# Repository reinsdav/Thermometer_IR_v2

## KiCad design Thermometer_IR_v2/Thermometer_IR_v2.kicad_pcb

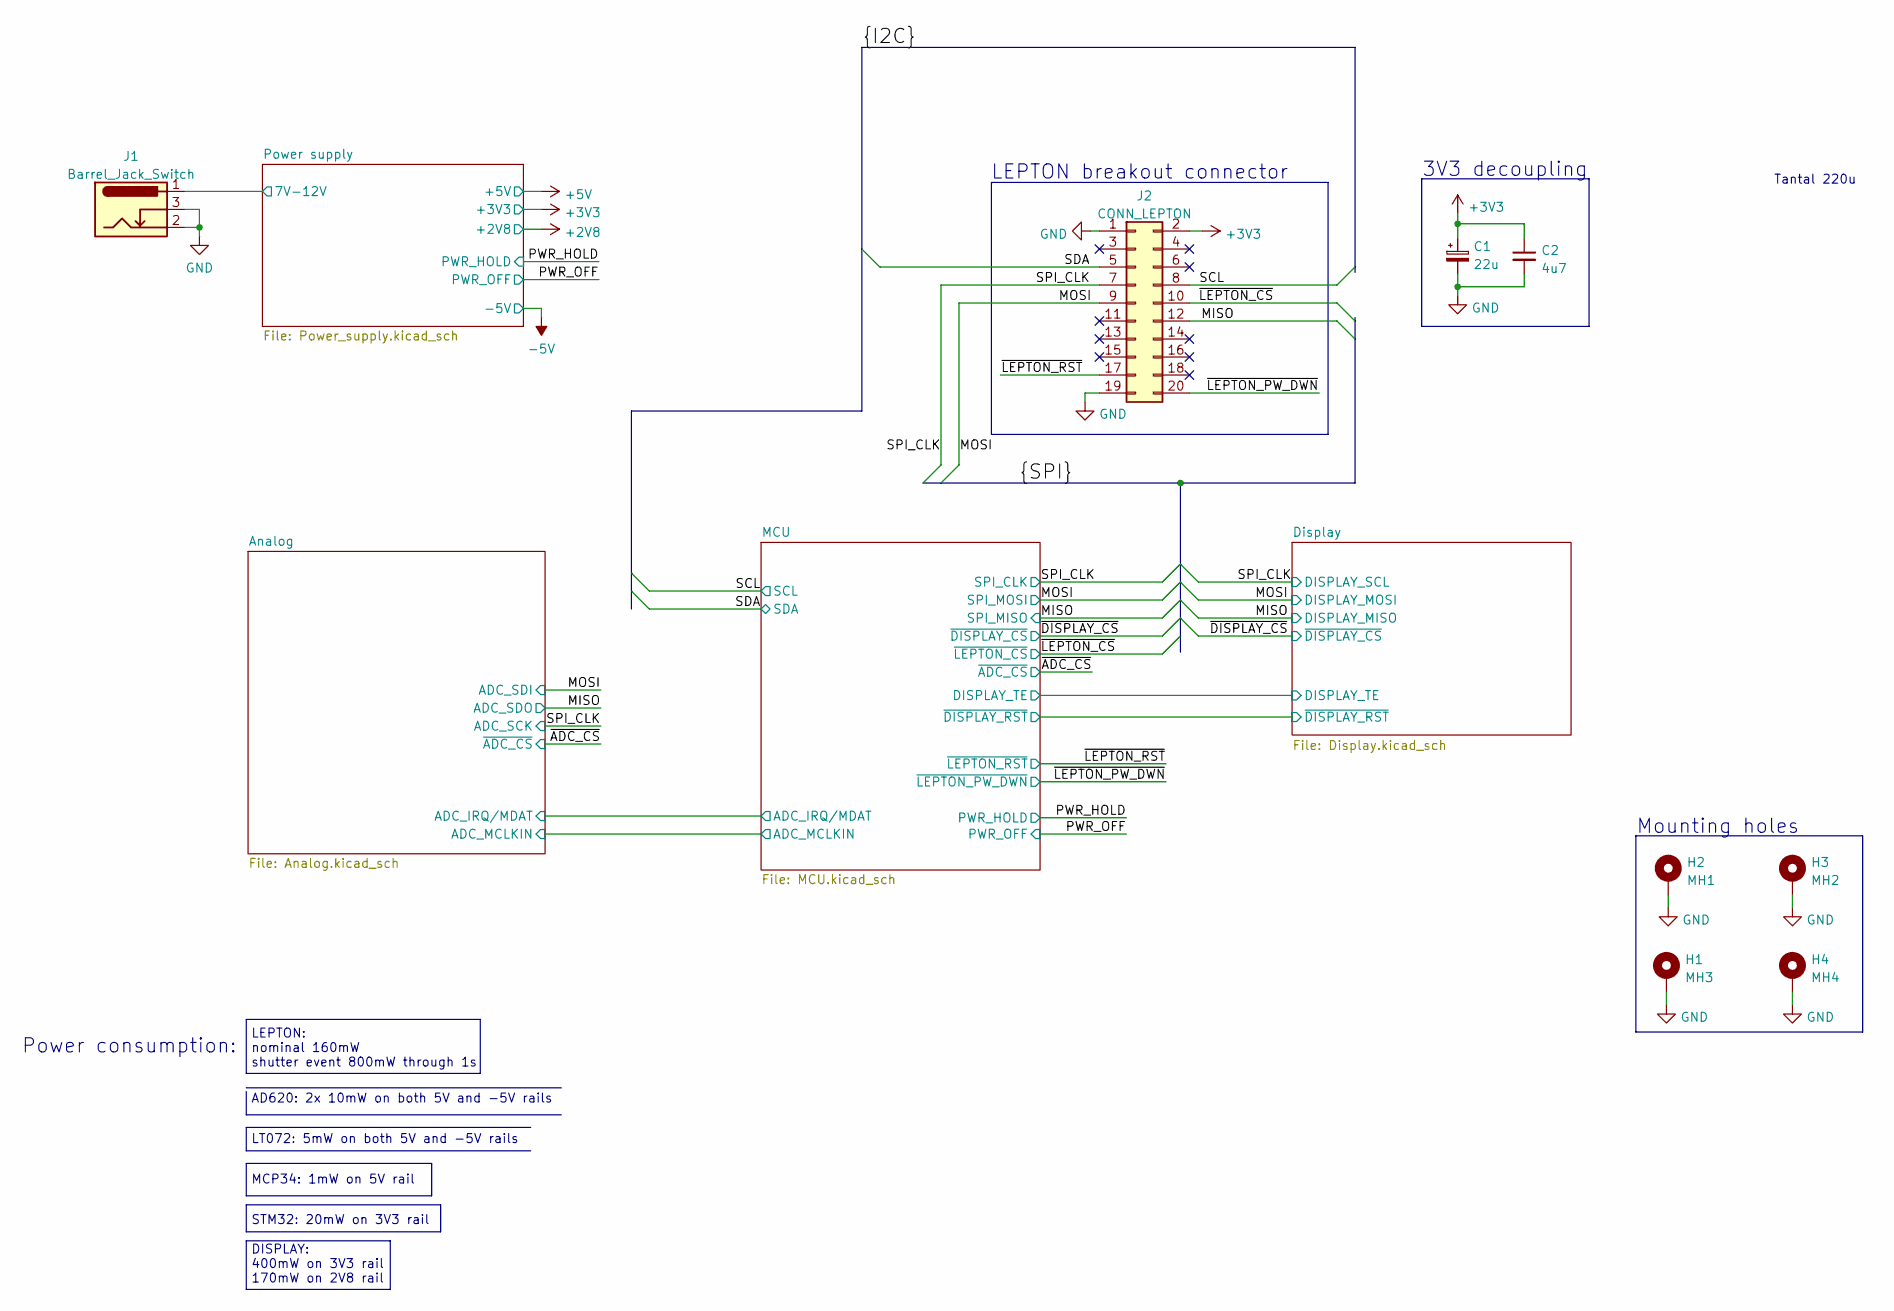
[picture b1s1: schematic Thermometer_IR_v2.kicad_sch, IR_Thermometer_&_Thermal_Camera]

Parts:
C1: 22u; CP_Elec_4x5.4
C2: 4u7; C_0805_2012Metric
H1: MH3; MountingHole_3mm_Pad_Via
H2: MH1; MountingHole_3mm_Pad_Via
H3: MH2; MountingHole_3mm_Pad_Via
H4: MH4; MountingHole_3mm_Pad_Via
J1: Barrel_Jack_Switch; BarrelJack_CLIFF_FC681465S_SMT_Horizontal
J2: CONN_LEPTON; PinSocket_2x10_P2.54mm_Horizontal

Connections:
+3V3: C1.1, C2.1, J2.2; also elsewhere on the board
/MISO: J2.12; also elsewhere on the board
/MOSI: J2.9; also elsewhere on the board
/Power supply/7V-12V: J1.1; also elsewhere on the board
/SCL: J2.8; also elsewhere on the board
/SDA: J2.5; also elsewhere on the board
/SPI_CLK: J2.7; also elsewhere on the board
/~LEPTON_CS: J2.10; also elsewhere on the board
/~LEPTON_PW_DWN: J2.20; also elsewhere on the board
/~LEPTON_RST: J2.17; also elsewhere on the board
GND: C1.2, C2.2, H1.1, H2.1, H3.1, H4.1, J1.2, J1.3, J2.1, J2.19; also elsewhere on the board

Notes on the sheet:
LT072: 5mW on both 5V and -5V rails
Power consumption:
STM32: 20mW on 3V3 rail
DISPLAY: 400mW on 3V3 rail 170mW on 2V8 rail
MCP34: 1mW on 5V rail
AD620: 2x 10mW on both 5V and -5V rails
3V3 decoupling
LEPTON breakout connector
Tantal 220u
LEPTON: nominal 160mW shutter event 800mW through 1s
Mounting holes

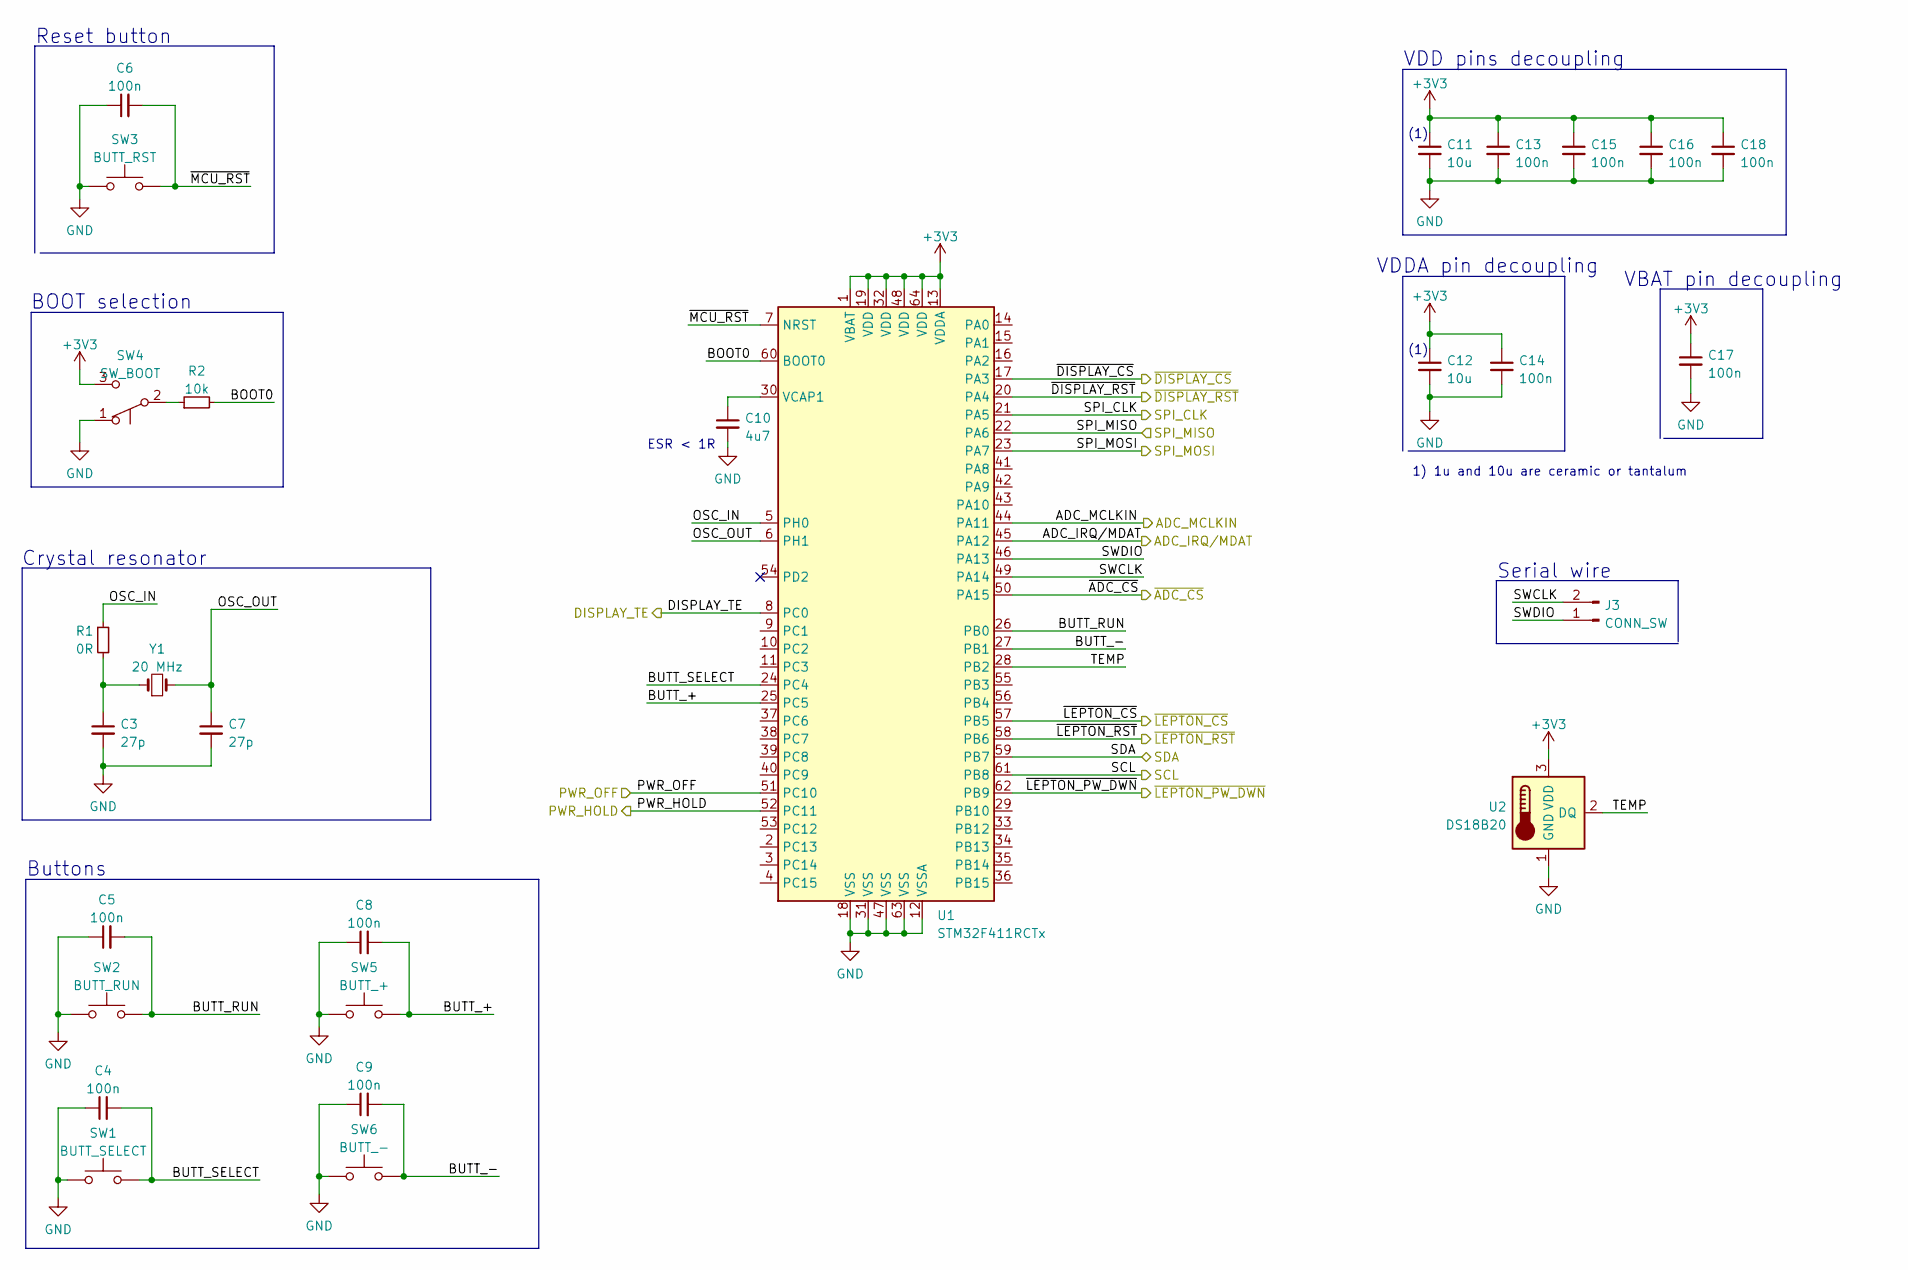
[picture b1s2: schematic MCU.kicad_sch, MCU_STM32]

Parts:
C3, C7: 27p; C_0805_2012Metric
C4, C5, C6, C8, C9, C13, C14, C15, C16, C17, C18: 100n; C_0805_2012Metric
C10: 4u7; C_0805_2012Metric
C11, C12: 10u; C_1206_3216Metric
J3: CONN_SW; PinHeader_1x02_P2.54mm_Vertical
R1: 0R; R_0805_2012Metric
R2: 10k; R_0805_2012Metric
SW1: BUTT_SELECT; SW_SPST_TL3305C
SW2: BUTT_RUN; SW_SPST_TL3305C
SW3: BUTT_RST; SW_SPST_TL3305C
SW4: SW_BOOT; SolderJumper-3_P1.3mm_Open_RoundedPad1.0x1.5mm_NumberLabels
SW5: BUTT_+; SW_SPST_TL3305C
SW6: BUTT_-; SW_SPST_TL3305C
U1: STM32F411RCTx; LQFP-64_10x10mm_P0.5mm
U2: DS18B20; TO-92_Inline
Y1: 20 MHz; Crystal_SMD_HC49-SD

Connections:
+3V3: C11.1, C12.1, C13.1, C14.1, C15.1, C16.1, C17.1, C18.1, SW4.3 (C), U1.1 (VBAT), U1.13 (VDDA), U1.19 (VDD), U1.32 (VDD), U1.48 (VDD), U1.64 (VDD), U2.3 (VDD); also elsewhere on the board
/Analog/ADC_IRQ/MDAT: U1.45 (PA12); also elsewhere on the board
/Analog/ADC_MCLKIN: U1.44 (PA11); also elsewhere on the board
/MCU/BOOT0: R2.2, U1.60 (BOOT0)
/MCU/BUTT_+: C8.2, SW5.2, U1.25 (PC5)
/MCU/BUTT_-: C9.2, SW6.2, U1.27 (PB1)
/MCU/BUTT_RUN: C5.2, SW2.2, U1.26 (PB0)
/MCU/BUTT_SELECT: C4.2, SW1.2, U1.24 (PC4)
/MCU/DISPLAY_TE: U1.8 (PC0); also elsewhere on the board
/MCU/OSC_IN: R1.1, U1.5 (PH0)
/MCU/OSC_OUT: C7.1, U1.6 (PH1), Y1.2
/MCU/SWCLK: J3.2, U1.49 (PA14)
/MCU/SWDIO: J3.1, U1.46 (PA13)
/MCU/TEMP: U1.28 (PB2), U2.2 (DQ)
/MCU/~DISPLAY_RST: U1.20 (PA4); also elsewhere on the board
/MCU/~MCU_RST: C6.2, SW3.2, U1.7 (NRST)
/MISO: U1.22 (PA6); also elsewhere on the board
/MOSI: U1.23 (PA7); also elsewhere on the board
/PWR_HOLD: U1.52 (PC11); also elsewhere on the board
/PWR_OFF: U1.51 (PC10); also elsewhere on the board
/SCL: U1.61 (PB8); also elsewhere on the board
/SDA: U1.59 (PB7); also elsewhere on the board
/SPI_CLK: U1.21 (PA5); also elsewhere on the board
/~ADC_CS: U1.50 (PA15); also elsewhere on the board
/~DISPLAY_CS: U1.17 (PA3); also elsewhere on the board
/~LEPTON_CS: U1.57 (PB5); also elsewhere on the board
/~LEPTON_PW_DWN: U1.62 (PB9); also elsewhere on the board
/~LEPTON_RST: U1.58 (PB6); also elsewhere on the board
GND: C3.2, C4.1, C5.1, C6.1, C7.2, C8.1, C9.1, C10.2, C11.2, C12.2, C13.2, C14.2, C15.2, C16.2, C17.2, C18.2, SW1.1, SW2.1, SW3.1, SW4.1 (A), SW5.1, SW6.1, U1.12 (VSSA), U1.18 (VSS), U1.31 (VSS), U1.47 (VSS), U1.63 (VSS), U2.1 (GND); also elsewhere on the board
unnamed: C3.1, R1.2, Y1.1
unnamed: C10.1, U1.30 (VCAP1)
unnamed: R2.1, SW4.2 (B)

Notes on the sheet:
Serial wire
VBAT pin decoupling
(1)
VDDA pin decoupling
1) 1u and 10u are ceramic or tantalum
BOOT selection
VDD pins decoupling
Buttons
Crystal resonator
Reset button
ESR < 1R

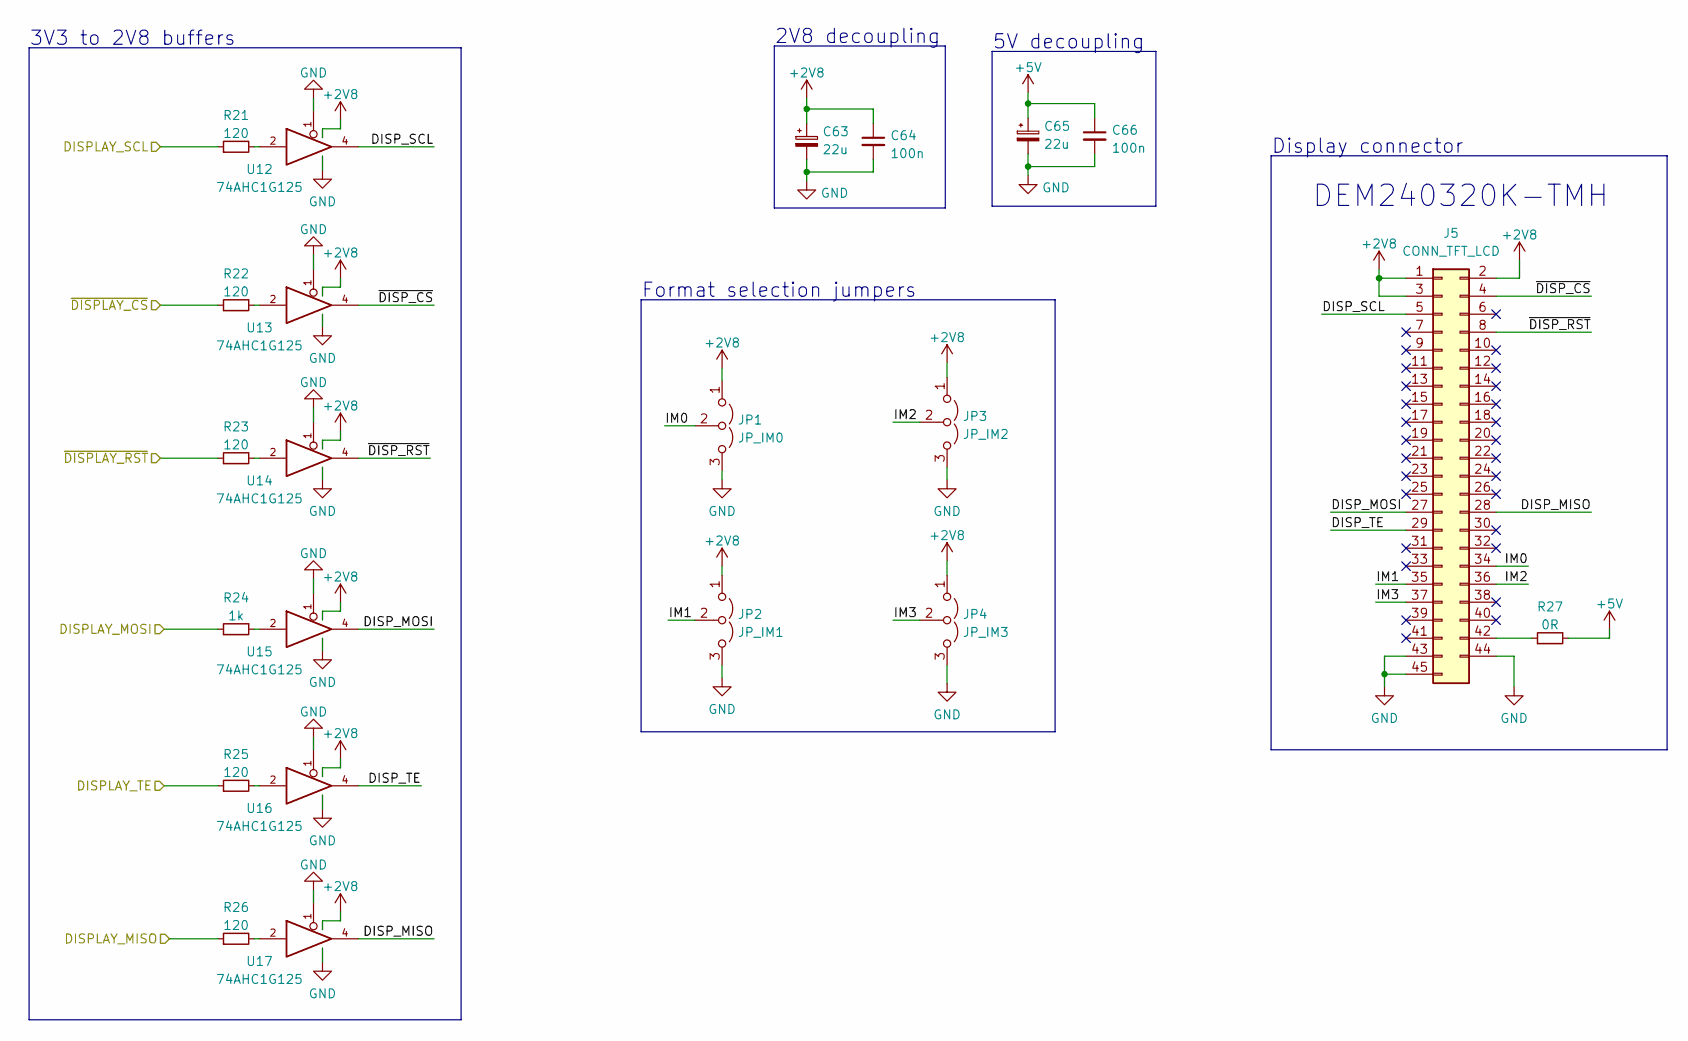
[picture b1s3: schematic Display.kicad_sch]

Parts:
C63, C65: 22u; CP_Elec_4x5.4
C64, C66: 100n; C_0805_2012Metric
J5: CONN_TFT_LCD; Hirose_FH12-45S-0.5SH_1x45-1MP_P0.50mm_Horizontal
JP1: JP_IM0; SolderJumper-3_P1.3mm_Open_RoundedPad1.0x1.5mm_NumberLabels
JP2: JP_IM1; SolderJumper-3_P1.3mm_Open_RoundedPad1.0x1.5mm_NumberLabels
JP3: JP_IM2; SolderJumper-3_P1.3mm_Open_RoundedPad1.0x1.5mm_NumberLabels
JP4: JP_IM3; SolderJumper-3_P1.3mm_Open_RoundedPad1.0x1.5mm_NumberLabels
R21, R22, R23, R25, R26: 120; R_0805_2012Metric
R24: 1k; R_0805_2012Metric
R27: 0R; R_0805_2012Metric
U12, U13, U14, U15, U16, U17: 74AHC1G125; SOT-353_SC-70-5

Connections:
+2V8: C63.1, C64.1, J5.1, J5.2, J5.3, JP1.1 (A), JP2.1 (A), JP3.1 (A), JP4.1 (A), U12.5 (VCC), U13.5 (VCC), U14.5 (VCC), U15.5 (VCC), U16.5 (VCC), U17.5 (VCC); also elsewhere on the board
+5V: C65.1, C66.1, R27.2; also elsewhere on the board
/Display/DISP_MISO: J5.28, U17.4
/Display/DISP_MOSI: J5.27, U15.4
/Display/DISP_SCL: J5.5, U12.4
/Display/DISP_TE: J5.29, U16.4
/Display/IM0: J5.34, JP1.2 (C)
/Display/IM1: J5.35, JP2.2 (C)
/Display/IM2: J5.36, JP3.2 (C)
/Display/IM3: J5.37, JP4.2 (C)
/Display/~DISP_CS: J5.4, U13.4
/Display/~DISP_RST: J5.8, U14.4
/MCU/DISPLAY_TE: R25.1; also elsewhere on the board
/MCU/~DISPLAY_RST: R23.1; also elsewhere on the board
/MISO: R26.1; also elsewhere on the board
/MOSI: R24.1; also elsewhere on the board
/SPI_CLK: R21.1; also elsewhere on the board
/~DISPLAY_CS: R22.1; also elsewhere on the board
GND: C63.2, C64.2, C65.2, C66.2, J5.43, J5.44, J5.45, JP1.3 (B), JP2.3 (B), JP3.3 (B), JP4.3 (B), U12.1, U12.3 (GND), U13.1, U13.3 (GND), U14.1, U14.3 (GND), U15.1, U15.3 (GND), U16.1, U16.3 (GND), U17.1, U17.3 (GND); also elsewhere on the board
unnamed: J5.42, R27.1
unnamed: R21.2, U12.2
unnamed: R22.2, U13.2
unnamed: R23.2, U14.2
unnamed: R24.2, U15.2
unnamed: R25.2, U16.2
unnamed: R26.2, U17.2

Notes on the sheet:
Display connector
DEM240320K-TMH
5V decoupling
Format selection jumpers
3V3 to 2V8 buffers
2V8 decoupling

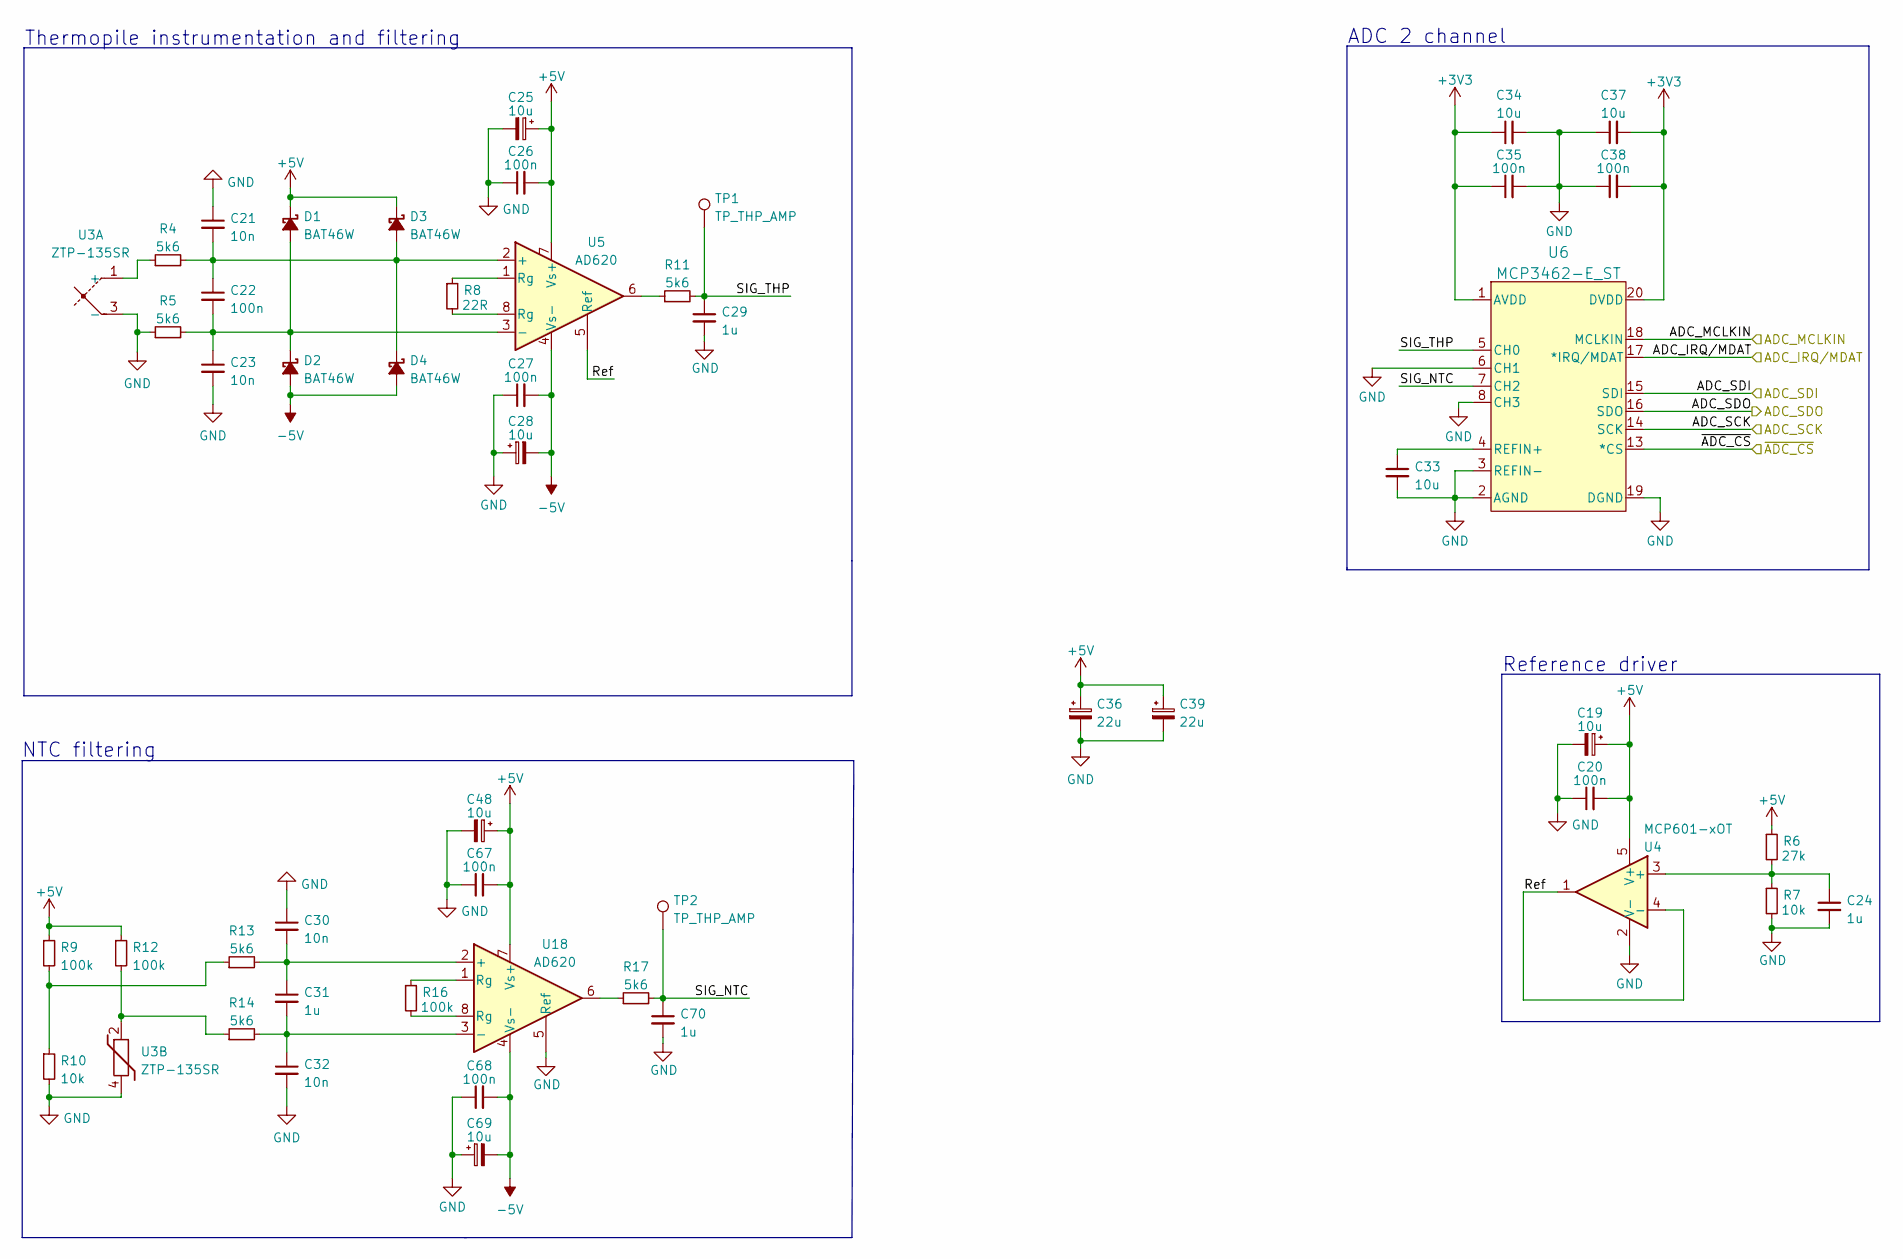
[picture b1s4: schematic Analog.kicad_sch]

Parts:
C19, C25, C28, C48, C69: 10u; C_1206_3216Metric
C20, C22, C26, C27, C35, C38, C67, C68: 100n; C_0805_2012Metric
C21, C23, C30, C32: 10n; C_0805_2012Metric
C24, C29, C31, C70: 1u; C_0805_2012Metric
C33, C34, C37: 10u; C_0805_2012Metric
C36, C39: 22u; CP_Elec_4x5.4
D1, D2, D3, D4: BAT46W; D_SOD-123F
R4, R5, R11, R13, R14, R17: 5k6; R_0805_2012Metric
R6: 27k; R_0805_2012Metric
R7, R10: 10k; R_0805_2012Metric
R8: 22R; R_0805_2012Metric
R9, R12, R16: 100k; R_0805_2012Metric
TP1, TP2: TP_THP_AMP; TestPoint_Pad_D2.0mm
U3: ZTP-135SR; TO-46-4
U4: MCP601-xOT; SOT-23-5
U5, U18: AD620; SOIC-8_3.9x4.9mm_P1.27mm
U6: MCP3462-E_ST; TSSOP-20_4.4x6.5mm_P0.65mm

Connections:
+3V3: C34.1, C35.1, C37.2, C38.2, U6.1 (AVDD), U6.20 (DVDD); also elsewhere on the board
+5V: C19.1, C20.2, C25.1, C26.2, C36.1, C39.1, C48.1, C67.2, D1.1 (K), D3.1 (K), R6.1, R9.1, R12.1, U4.5 (V+), U5.7 (Vs+), U18.7 (Vs+); also elsewhere on the board
-5V: C27.2, C28.2, C68.2, C69.2, D2.2 (A), D4.2 (A), U5.4 (Vs-), U18.4 (Vs-); also elsewhere on the board
/Analog/ADC_IRQ/MDAT: U6.17 (*IRQ/MDAT); also elsewhere on the board
/Analog/ADC_MCLKIN: U6.18 (MCLKIN); also elsewhere on the board
/Analog/Ref: U4.1, U4.4 (-), U5.5 (Ref)
/Analog/SIG_NTC: C70.1, R17.2, TP2.1, U6.7 (CH2)
/Analog/SIG_THP: C29.1, R11.2, TP1.1, U6.5 (CH0)
/MISO: U6.16 (SDO); also elsewhere on the board
/MOSI: U6.15 (SDI); also elsewhere on the board
/SPI_CLK: U6.14 (SCK); also elsewhere on the board
/~ADC_CS: U6.13 (*CS); also elsewhere on the board
GND: C19.2, C20.1, C21.1, C23.2, C24.2, C25.2, C26.1, C27.1, C28.1, C29.2, C30.1, C32.2, C33.2, C34.2, C35.2, C36.2, C37.1, C38.1, C39.2, C48.2, C67.1, C68.1, C69.1, C70.2, R5.1, R7.2, R10.2, U3.3 (-), U3.4, U4.2 (V-), U6.2 (AGND), U6.3 (REFIN-), U6.6 (CH1), U6.8 (CH3), U6.19 (DGND), U18.5 (Ref); also elsewhere on the board
unnamed: C21.2, C22.1, D3.2 (A), D4.1 (K), R4.2, U5.2 (+)
unnamed: C22.2, C23.1, D1.2 (A), D2.1 (K), R5.2, U5.3 (-)
unnamed: C24.1, R6.2, R7.1, U4.3 (+)
unnamed: C30.2, C31.1, R13.2, U18.2 (+)
unnamed: C31.2, C32.1, R14.2, U18.3 (-)
unnamed: C33.1, U6.4 (REFIN+)
unnamed: R4.1, U3.1 (+)
unnamed: R8.1, U5.1 (Rg)
unnamed: R8.2, U5.8 (Rg)
unnamed: R9.2, R10.1, R13.1
unnamed: R11.1, U5.6
unnamed: R12.2, R14.1, U3.2
unnamed: R16.1, U18.1 (Rg)
unnamed: R16.2, U18.8 (Rg)
unnamed: R17.1, U18.6

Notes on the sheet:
Reference driver
ADC 2 channel
Thermopile instrumentation and filtering
NTC filtering

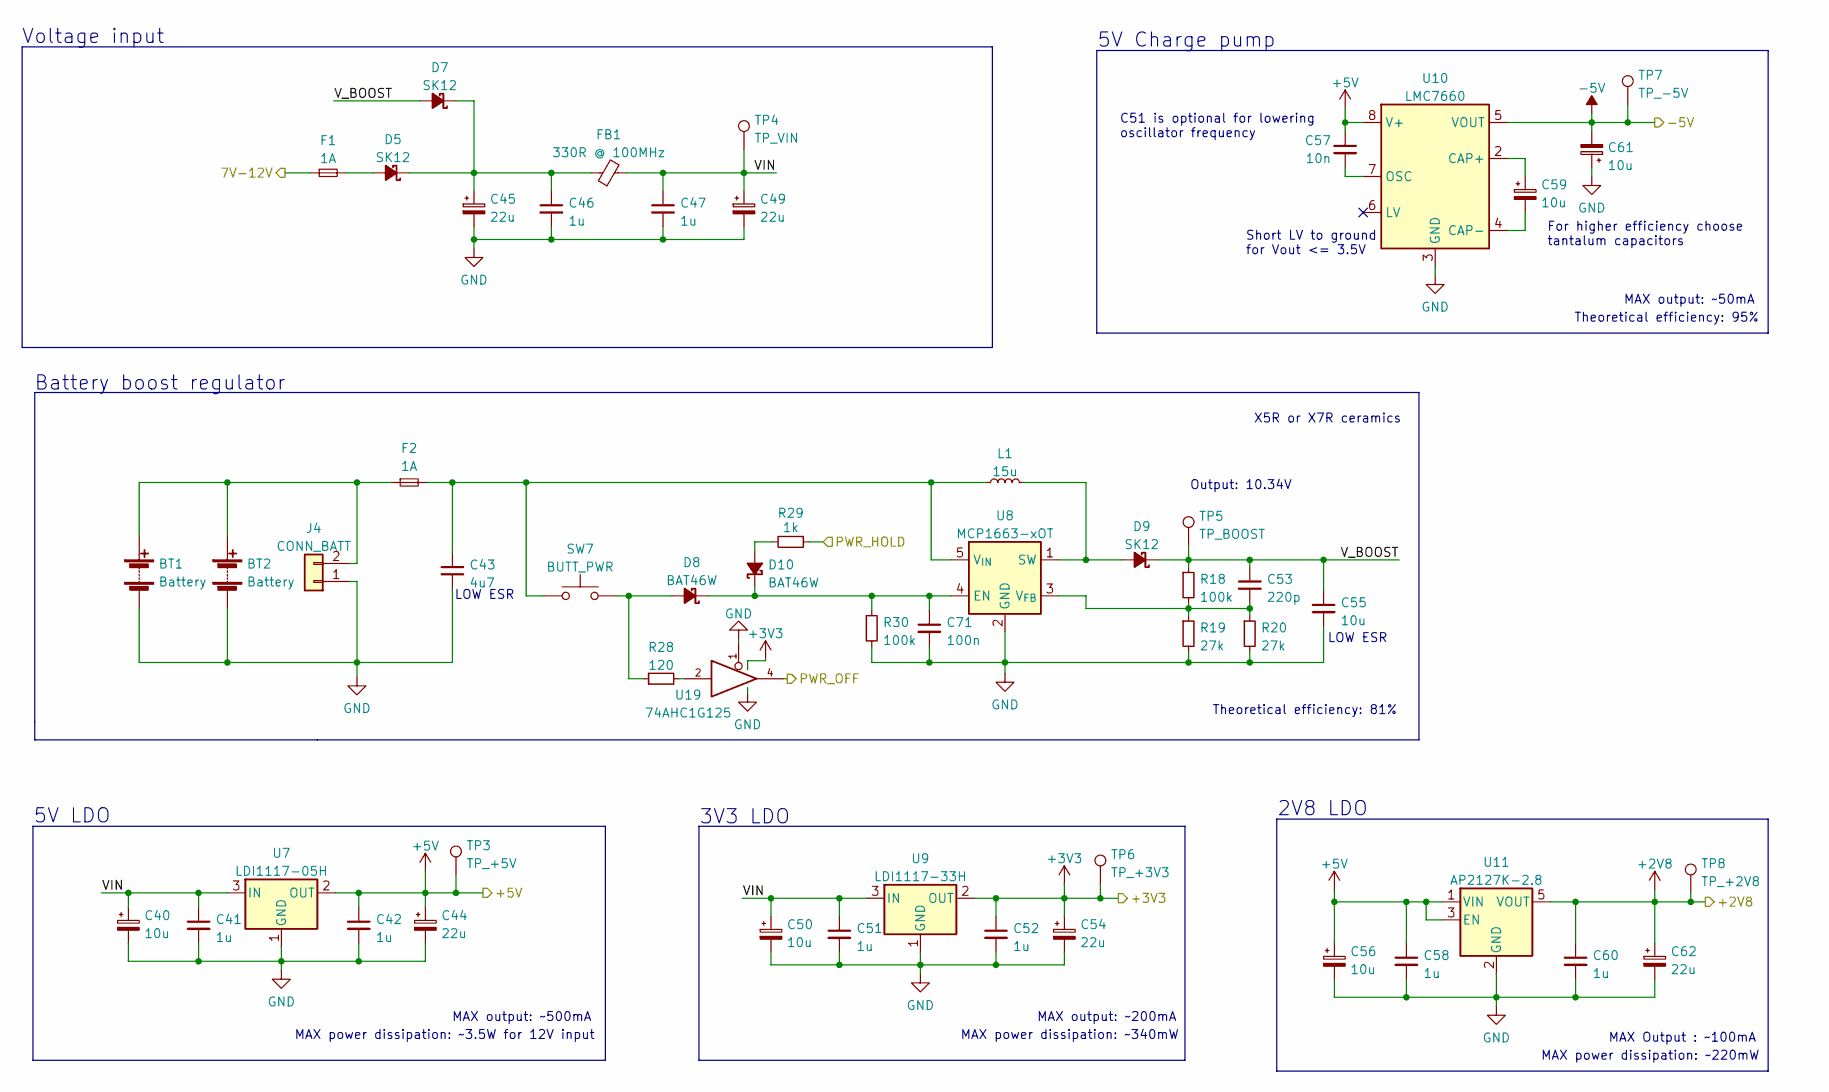
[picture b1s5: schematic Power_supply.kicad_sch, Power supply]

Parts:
BT1, BT2: Battery
C40, C50, C56, C59, C61: 10u; C_1206_3216Metric
C41, C42, C46, C47, C51, C52, C58, C60: 1u; C_0805_2012Metric
C43: 4u7; C_0805_2012Metric
C44, C54, C62: 22u; C_1206_3216Metric
C45, C49: 22u; CP_Elec_4x5.4
C53: 220p; C_0805_2012Metric
C55: 10u; C_0805_2012Metric
C57: 10n; C_0805_2012Metric
C71: 100n; C_0805_2012Metric
D5, D7, D9: SK12; D_SMA
D8, D10: BAT46W; D_SOD-123F
F1, F2: 1A; Fuse_1206_3216Metric
FB1: 330R @ 100MHz; L_0805_2012Metric
J4: CONN_BATT; TerminalBlock_bornier-2_P5.08mm
L1: 15u; L_7.3x7.3_H3.5
R18, R30: 100k; R_0805_2012Metric
R19, R20: 27k; R_0805_2012Metric
R28: 120; R_0805_2012Metric
R29: 1k; R_0805_2012Metric
SW7: BUTT_PWR; SW_SPST_TL3305C
TP3: TP_+5V; TestPoint_Pad_D2.0mm
TP4: TP_VIN; TestPoint_Pad_D2.0mm
TP5: TP_BOOST; TestPoint_Pad_D2.0mm
TP6: TP_+3V3; TestPoint_Pad_D2.0mm
TP7: TP_-5V; TestPoint_Pad_D2.0mm
TP8: TP_+2V8; TestPoint_Pad_D2.0mm
U7: LDI1117-05H; SOT-223
U8: MCP1663-xOT; SOT-23-5
U9: LDI1117-33H; SOT-223
U10: LMC7660; SOIC-8_3.9x4.9mm_P1.27mm
U11: AP2127K-2.8; SOT-23-5
U19: 74AHC1G125; SOT-353_SC-70-5

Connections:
+2V8: C60.1, C62.1, TP8.1, U11.5 (VOUT); also elsewhere on the board
+3V3: C52.1, C54.1, TP6.1, U9.2 (OUT), U9.4, U19.5 (VCC); also elsewhere on the board
+5V: C42.1, C44.1, C56.1, C57.1, C58.1, TP3.1, U7.2 (OUT), U7.4, U10.8 (V+), U11.1 (VIN), U11.3 (EN); also elsewhere on the board
-5V: C61.2, TP7.1, U10.5 (VOUT); also elsewhere on the board
/PWR_HOLD: R29.1; also elsewhere on the board
/PWR_OFF: U19.4; also elsewhere on the board
/Power supply/7V-12V: F1.1; also elsewhere on the board
/Power supply/VIN: C40.1, C41.1, C47.1, C49.1, C50.1, C51.1, FB1.2, TP4.1, U7.3 (IN), U9.3 (IN)
/Power supply/V_BOOST: C53.1, C55.1, D7.2 (A), D9.1 (K), R18.1, TP5.1
GND: BT1.2 (-), BT2.2 (-), C40.2, C41.2, C42.2, C43.2, C44.2, C45.2, C46.2, C47.2, C49.2, C50.2, C51.2, C52.2, C54.2, C55.2, C56.2, C58.2, C60.2, C61.1, C62.2, C71.2, J4.1, R19.2, R20.2, R30.2, U7.1 (GND), U8.2 (GND), U9.1 (GND), U10.3 (GND), U11.2 (GND), U19.1, U19.3 (GND); also elsewhere on the board
unnamed: BT1.1 (+), BT2.1 (+), F2.1, J4.2
unnamed: C43.1, F2.2, L1.1, SW7.1, U8.5 (V_{IN})
unnamed: C45.1, C46.1, D5.1 (K), D7.1 (K), FB1.1
unnamed: C53.2, R18.2, R19.1, R20.1, U8.3 (V_{FB})
unnamed: C57.2, U10.7 (OSC)
unnamed: C59.1, U10.2 (CAP+)
unnamed: C59.2, U10.4 (CAP-)
unnamed: D5.2 (A), F1.2
unnamed: D8.2 (A), R28.1, SW7.2
unnamed: D10.2 (A), R29.2
unnamed: D9.2 (A), L1.2, U8.1 (SW)
unnamed: R28.2, U19.2
unnamed: C71.1, D8.1 (K), D10.1 (K), R30.1, U8.4 (EN)

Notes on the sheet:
5V Charge pump
Battery boost regulator
2V8 LDO
MAX output: ~50mA
For higher efficiency choose tantalum capacitors
Short LV to ground for Vout <= 3.5V
MAX output: ~500mA
MAX output: ~200mA
Theoretical efficiency: 95%
5V LDO
LOW ESR
X5R or X7R ceramics
MAX power dissipation: ~3.5W for 12V input
C51 is optional for lowering oscillator frequency
MAX Output : ~100mA
Theoretical efficiency: 81%
Output: 10.34V
3V3 LDO
MAX power dissipation: ~340mW
Voltage input
MAX power dissipation: ~220mW

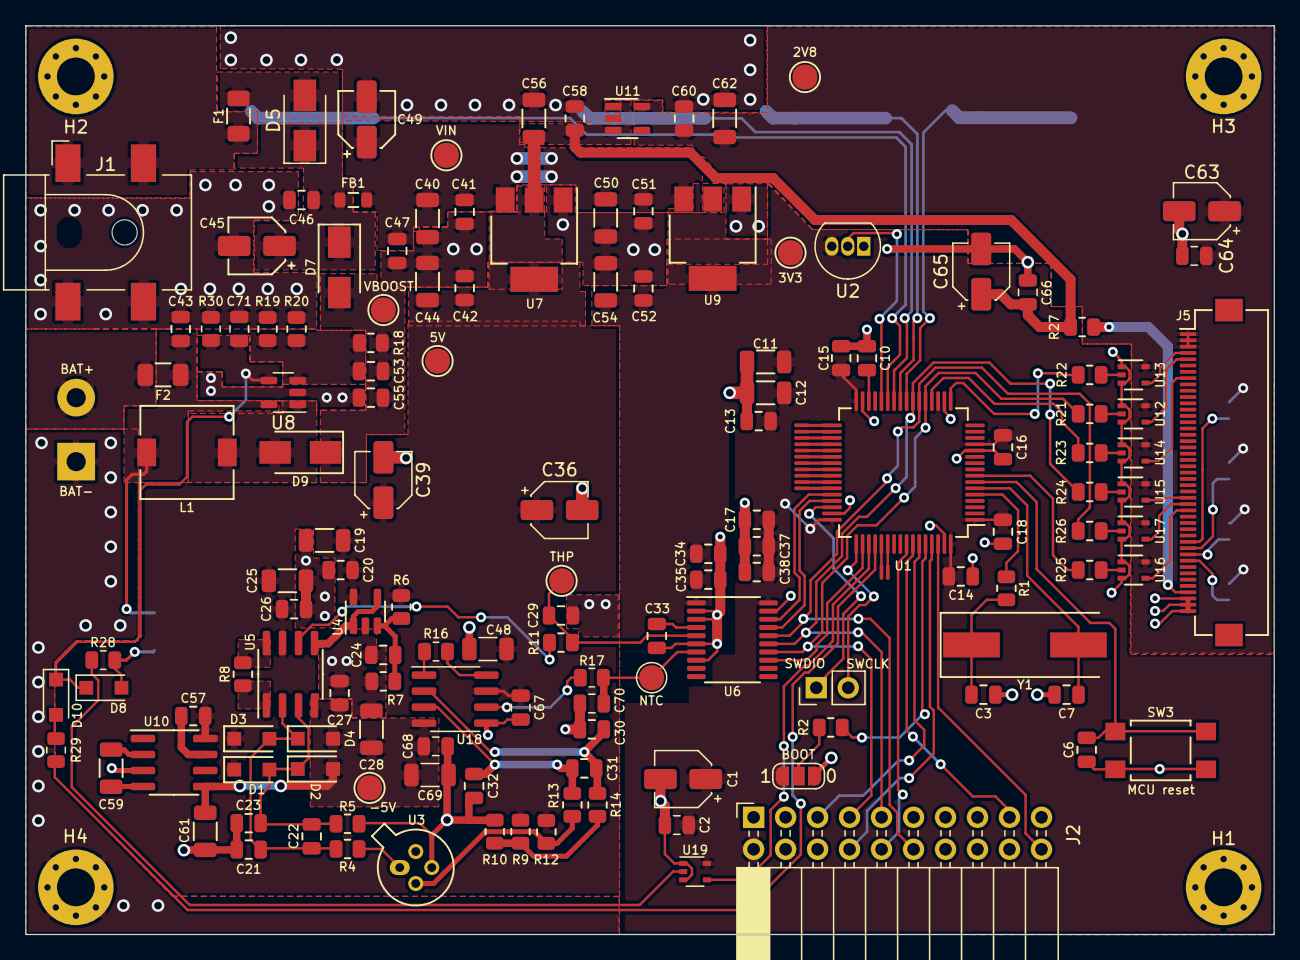
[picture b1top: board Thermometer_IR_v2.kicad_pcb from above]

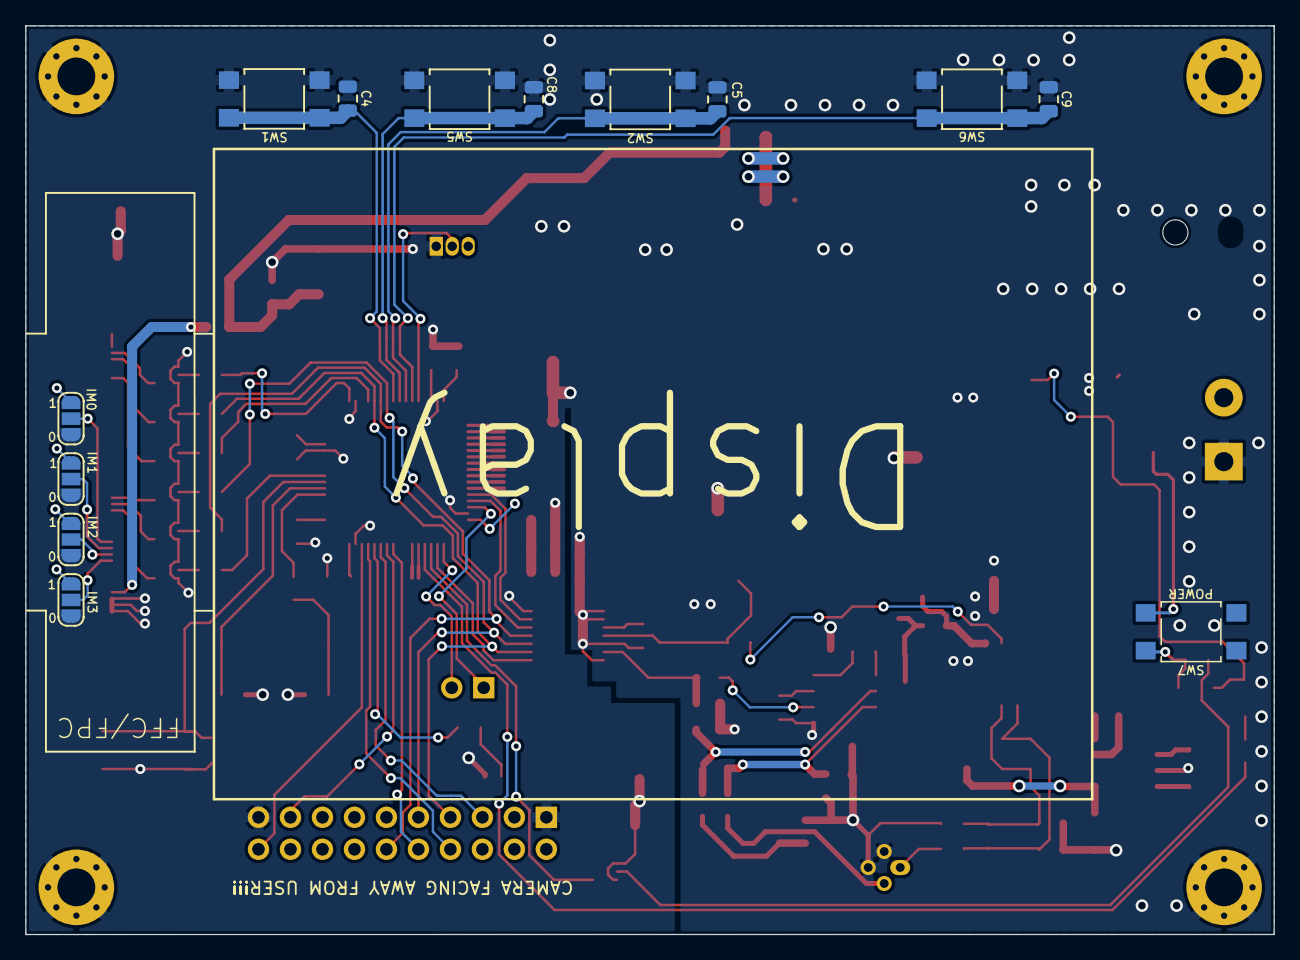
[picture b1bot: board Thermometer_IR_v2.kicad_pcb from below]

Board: 2 copper layers, 99.1 x 72.2 mm, 160 parts (13 on the bottom side), 86 nets.

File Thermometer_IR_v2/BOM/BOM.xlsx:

Reference | Quantity | Value | Footprint | TME
BT1 BT2 | 2 | Battery |  | BH-331A
C1 C36 C39 C45 C49 C63 C65 | 7 | 22u | Capacitor_SMD:CP_Elec_4x5.4 | VS1C220MB054000CE0
C11 C12 C19 C25 C28 C40 C48 C50 C56 C59 C61 C69 | 12 | 10u | Capacitor_SMD:C_1206_3216Metric | TAJA106K016R
C2 C10 C43 | 3 | 4u7 | Capacitor_SMD:C_0805_2012Metric | 0805X475K6R3CT
C21 C23 C30 C32 C57 | 5 | 10n | Capacitor_SMD:C_0805_2012Metric | 0805N103J500
C24 C29 C31 C41 C42 C46 C47 C51 C52 C58 C60 C70 | 12 | 1u | Capacitor_SMD:C_0805_2012Metric | GCM21BR71E105KA56K
C3 C7 | 2 | 27p | Capacitor_SMD:C_0805_2012Metric | CL10C270JB8NNNC
C33 C34 C37 C55 | 4 | 10u | Capacitor_SMD:C_0805_2012Metric | GRM21BR61E106KA73L
C4 C5 C6 C8 C9 C13 C14 C15 C16 C17 C18 C20 C22 C26 C27 C35 C38 C64 C66 C67 C68 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 | 22 | 100n | Capacitor_SMD:C_0805_2012Metric | 0805B104J101CT
C44 C54 C62 | 3 | 22u | Capacitor_SMD:C_1206_3216Metric | 293D226X96R3A2TE3
C53 | 1 | 220p | Capacitor_SMD:C_0805_2012Metric | C0805C221M5RACTU
D1 D2 D3 D4 D8 D10 | 6 | BAT46W | Diode_SMD:D_SOD-123F | BAT46W-DIO
D5 D7 D9 | 3 | SK12 | Diode_SMD:D_SMA | SK12-DIO
F1 F2 | 2 | 1A | Fuse:Fuse_1206_3216Metric | ERBRG1R00V
FB1 | 1 | 330R @ 100MHz | Inductor_SMD:L_0805_2012Metric | BLM21PG331SN1D
H1 | 1 | MH3 | MountingHole:MountingHole_3mm_Pad_Via
H2 | 1 | MH1 | MountingHole:MountingHole_3mm_Pad_Via
H3 | 1 | MH2 | MountingHole:MountingHole_3mm_Pad_Via
H4 | 1 | MH4 | MountingHole:MountingHole_3mm_Pad_Via
J1 | 1 | Barrel_Jack_Switch | Connector_BarrelJack:BarrelJack_CLIFF_FC681465S_SMT_Horizontal | FC68148S
J2 | 1 | CONN_LEPTON | Connector_PinSocket_2.54mm:PinSocket_2x10_P2.54mm_Horizontal | ZL263-40DG
J3 | 1 | CONN_SW | Connector_PinHeader_2.54mm:PinHeader_1x02_P2.54mm_Vertical
J4 | 1 | CONN_BATT | TerminalBlock:TerminalBlock_bornier-2_P5.08mm
J5 | 1 | CONN_TFT_LCD | Connector_FFC-FPC:Hirose_FH12-45S-0.5SH_1x45-1MP_P0.50mm_Horizontal | FH12-45S-0.5SH-55
JP1 | 1 | JP_IM0 | Jumper:SolderJumper-3_P1.3mm_Open_RoundedPad1.0x1.5mm_NumberLabels
JP2 | 1 | JP_IM1 | Jumper:SolderJumper-3_P1.3mm_Open_RoundedPad1.0x1.5mm_NumberLabels
JP3 | 1 | JP_IM2 | Jumper:SolderJumper-3_P1.3mm_Open_RoundedPad1.0x1.5mm_NumberLabels
JP4 | 1 | JP_IM3 | Jumper:SolderJumper-3_P1.3mm_Open_RoundedPad1.0x1.5mm_NumberLabels
L1 | 1 | 15u | Inductor_SMD:L_7.3x7.3_H3.5 | DE0704-15
R1 R27 | 2 | 0R | Resistor_SMD:R_0805_2012Metric
R2 R7 R10 | 3 | 10k | Resistor_SMD:R_0805_2012Metric | ERA6AEB562V
R21 R22 R23 R25 R26 R28 | 6 | 120 | Resistor_SMD:R_0805_2012Metric | ERA6AEB121V
R24 R29 | 2 | 1k | Resistor_SMD:R_0805_2012Metric | ERA6AEB102V
R4 R5 R11 R13 R14 R17 | 6 | 5k6 | Resistor_SMD:R_0805_2012Metric | ERA6AEB562V
R6 R19 R20 | 3 | 27k | Resistor_SMD:R_0805_2012Metric | AR0805-27K-0.1%
R8 | 1 | 20R | Resistor_SMD:R_0805_2012Metric | AR0805-22R-0.1%
R9 R12 R16 R18 R30 | 5 | 100k | Resistor_SMD:R_0805_2012Metric | ERA6AEB104V
SW1 | 1 | BUTT_SELECT | Button_Switch_SMD:SW_SPST_TL3305C | TL3305BF160QG
SW2 | 1 | BUTT_RUN | Button_Switch_SMD:SW_SPST_TL3305C | TL3305BF160QG
SW3 | 1 | BUTT_RST | Button_Switch_SMD:SW_SPST_TL3305C | TL3305BF160QG
SW4 | 1 | SW_BOOT | Jumper:SolderJumper-3_P1.3mm_Open_RoundedPad1.0x1.5mm_NumberLabels
SW5 | 1 | BUTT_+ | Button_Switch_SMD:SW_SPST_TL3305C | TL3305BF160QG
SW6 | 1 | BUTT_- | Button_Switch_SMD:SW_SPST_TL3305C | TL3305BF160QG
SW7 | 1 | BUTT_PWR | Button_Switch_SMD:SW_SPST_TL3305C | TL3305BF160QG
TP1 TP2 | 2 | TP_THP_AMP | TestPoint:TestPoint_Pad_D2.0mm
TP3 | 1 | TP_+5V | TestPoint:TestPoint_Pad_D2.0mm
TP4 | 1 | TP_VIN | TestPoint:TestPoint_Pad_D2.0mm
TP5 | 1 | TP_BOOST | TestPoint:TestPoint_Pad_D2.0mm
TP6 | 1 | TP_+3V3 | TestPoint:TestPoint_Pad_D2.0mm
TP7 | 1 | TP_-5V | TestPoint:TestPoint_Pad_D2.0mm
TP8 | 1 | TP_+2V8 | TestPoint:TestPoint_Pad_D2.0mm
U1 | 1 | STM32F411RCTx | Package_QFP:LQFP-64_10x10mm_P0.5mm | STM32F411RET6
U10 | 1 | LMC7660 | Package_SO:SOIC-8_3.9x4.9mm_P1.27mm | LMC7660IMX/NOPB
U11 | 1 | AP2127K-2.8 | Package_TO_SOT_SMD:SOT-23-5 | AP2127K-2.8TRG1
U12 U13 U14 U15 U16 U17 U19 | 7 | 74AHC1G125 | Package_TO_SOT_SMD:SOT-353_SC-70-5 | 74AHC1G125SE-7
U2 | 1 | DS18B20 | Package_TO_SOT_THT:TO-92_Inline | DS18B20+
U3 | 1 | ZTP-135SR | Package_TO_SOT_THT:TO-46-4
U4 | 1 | MCP601-xOT | Package_TO_SOT_SMD:SOT-23-5
U5 U18 | 2 | AD620 | Package_SO:SOIC-8_3.9x4.9mm_P1.27mm
U6 | 1 | MCP3462-E_ST | Package_SO:TSSOP-20_4.4x6.5mm_P0.65mm | MCP3462R-E/ST
U7 | 1 | LDI1117-05H | Package_TO_SOT_SMD:SOT-223 | LDI1117-05H-DIO
U8 | 1 | MCP1663-xOT | Package_TO_SOT_SMD:SOT-23-5 | LMR62014XMF/NOPB
U9 | 1 | LDI1117-33H | Package_TO_SOT_SMD:SOT-223 | LDI1117-3.3D-DIO
Y1 | 1 | 20 MHz | Crystal:Crystal_SMD_HC49-SD | 20.00M-SMDHC49S
